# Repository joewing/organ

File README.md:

# 3D Printed Polyphonic Organ

## Features
  * Full-size 3D printed keyboard
  * 8-way polyphony
  * 9 drawbars to adjust harmonics (like a Hammond organ)
  * Sustain pedal
  * Range C0 through B7 (96 notes)

## Directories
  * src - Source code for the microcontroller (AVR ATtiny861A)
  * pcb/sensor - PCB for the key sensor board
  * pcb/controller PCB for the controller board
  * scad - OpenSCAD design

## Function Keys

Holding the "function" key on the controller PCB switches into
function mode.

### Tuning

Since we use the on-board oscillator, it is necessary to tune the
clock frequency to make the notes in tune. This tuning is stored in
EEPROM.

  * F#0 - Flatten
  * G#0 - Reset
  * A#0 - Sharpen

## 3D Printed Parts

  * Keybed
  * White keys (7)
  * Black keys (5)
  * Assembly tool (to help attach the rubber bands)
  * Control board holder

The sensor PCB is snapped into the keybed and the keys are attached,
one at a time along with the rubber band to pull the key up. Multiple
keybeds can be attached together using zipties (there are holes for
zipties in the standoff for the keys).

## BOM

  * Controller PCB
    * 1x ATtiny861A
    * 1x USB-B socket
    * 1x 2x3 IDC socket
    * 1x 3.5mm audio jack
    * 1x 3mm LED
    * 1x 6mm SPST tactile switch
    * 10x 10k linear POT
    * 2x 1k resistor
    * 12x 0.1u capacitor
    * 1x 10u capacitor
    * 1x 47u capacitor
    * 1x 6-pin right-angle socket

  * Sensor PCB (1 per octave)
    * 12x 12.6x6.5x5.7mm SPDT limit switch
    * 2x 10k resistor
    * 2x 74HC165
    * 2x 0.1uF capacitor
    * 1x 6-pin right-angle socket
    * 1x 6-pin right-angle pin header

  * Other
    * 12x small rubber bands (one set per octave)
    * USB cord and power supply

## Keys

Each note is controlled by a limit switch. The output of the limit
switches are processed serially using two 74HC165 8-bit parallel input
shift registers per octave. Since there are only 12 notes in an octave
4 bits are wasted for simplicity. Using this shift register interface,
we can read all keys using only 3 pins of the microcontroller.

In software, the state of each key is recorded in a bitmap. When a new key
press is detected, a "voice" is removed from the head of a linked list
and placed at the end of the list. The frequency increment is set
according to the index of the key that was pressed. The frequency increment
is a 16-bit value used to move through the waveform every time the
sample interrupt executes. The top 8 bits are used as an index into
the 256 entry waveform.

When a key release is detected, the "voice" is removed and placed at the
head of the list and the frequency increment is set to 0 to prevent the
sample interrupt from moving through the waveform.
The linked list is used so that the least recently pressed key is
re-used if there are too many keys pressed at the same time.

Finally, the sustain pedal simply prevents the processing of key releases.

## Drawbars

There are nine drawbars (potentiometers) that are sampled using the 
multiplexed ADC. One drawbar is sampled per iteration of the main loop.
We track the quantized value of each drawbar. When a change is
detected, its value is recorded and the waveform is recomputed.

## Waves

Waveforms are generated by sampling a 256 point sine wave.
The base waveform is at half the fundamental frequency (16')
allowing us to generate the necessary harmonics by stepping
through the sine wave at different rates:

  * 16'     - Sub-Octave (1x)
  * 5 1/3'  - Quint (3x)
  * 8'      - Principal (2x)
  * 4'      - Octave (4x)
  * 2 2/3'  - Nazard (6x)
  * 2'      - Super Octave (8x)
  * 1 3/5'  - Tierce (10x)
  * 1 1/3'  - Larigot (12x)
  * 1'      - Super-Super Octave (16x)

When a drawbar is changed, the waveform is recomputed by adding
together the scaled contributions from each drawbar. Each
contribution is determined by stepping through the sine wave at the
specified rate (2 for 8', etc), wrapping around when necessary,
and scaling the amplitude by the drawbar level. The final waveform
is scaled down by the max total contribution.
The waveform itself is stored as 256 8-bit values.

Audio is generated using 64 MHz pulse-width modulation. The duty cycle
is configured to have 256 levels, leaving an output frequency of 250 kHz,
which is well above the audio range and easy to filter. The duty cycle is
determined by adding together the waveform contributions from each voice.
Since there are 8 voices and the duty cycle is controlled by
an 8-bit value, we get 5 bits of resolution (this avoids overflow in
the case all voices are at the maximum position in the waveform at
the same time).
A 20 kHz timer interrupt causes us to move through the waveforms
for each voice and update the PWM duty cycle.

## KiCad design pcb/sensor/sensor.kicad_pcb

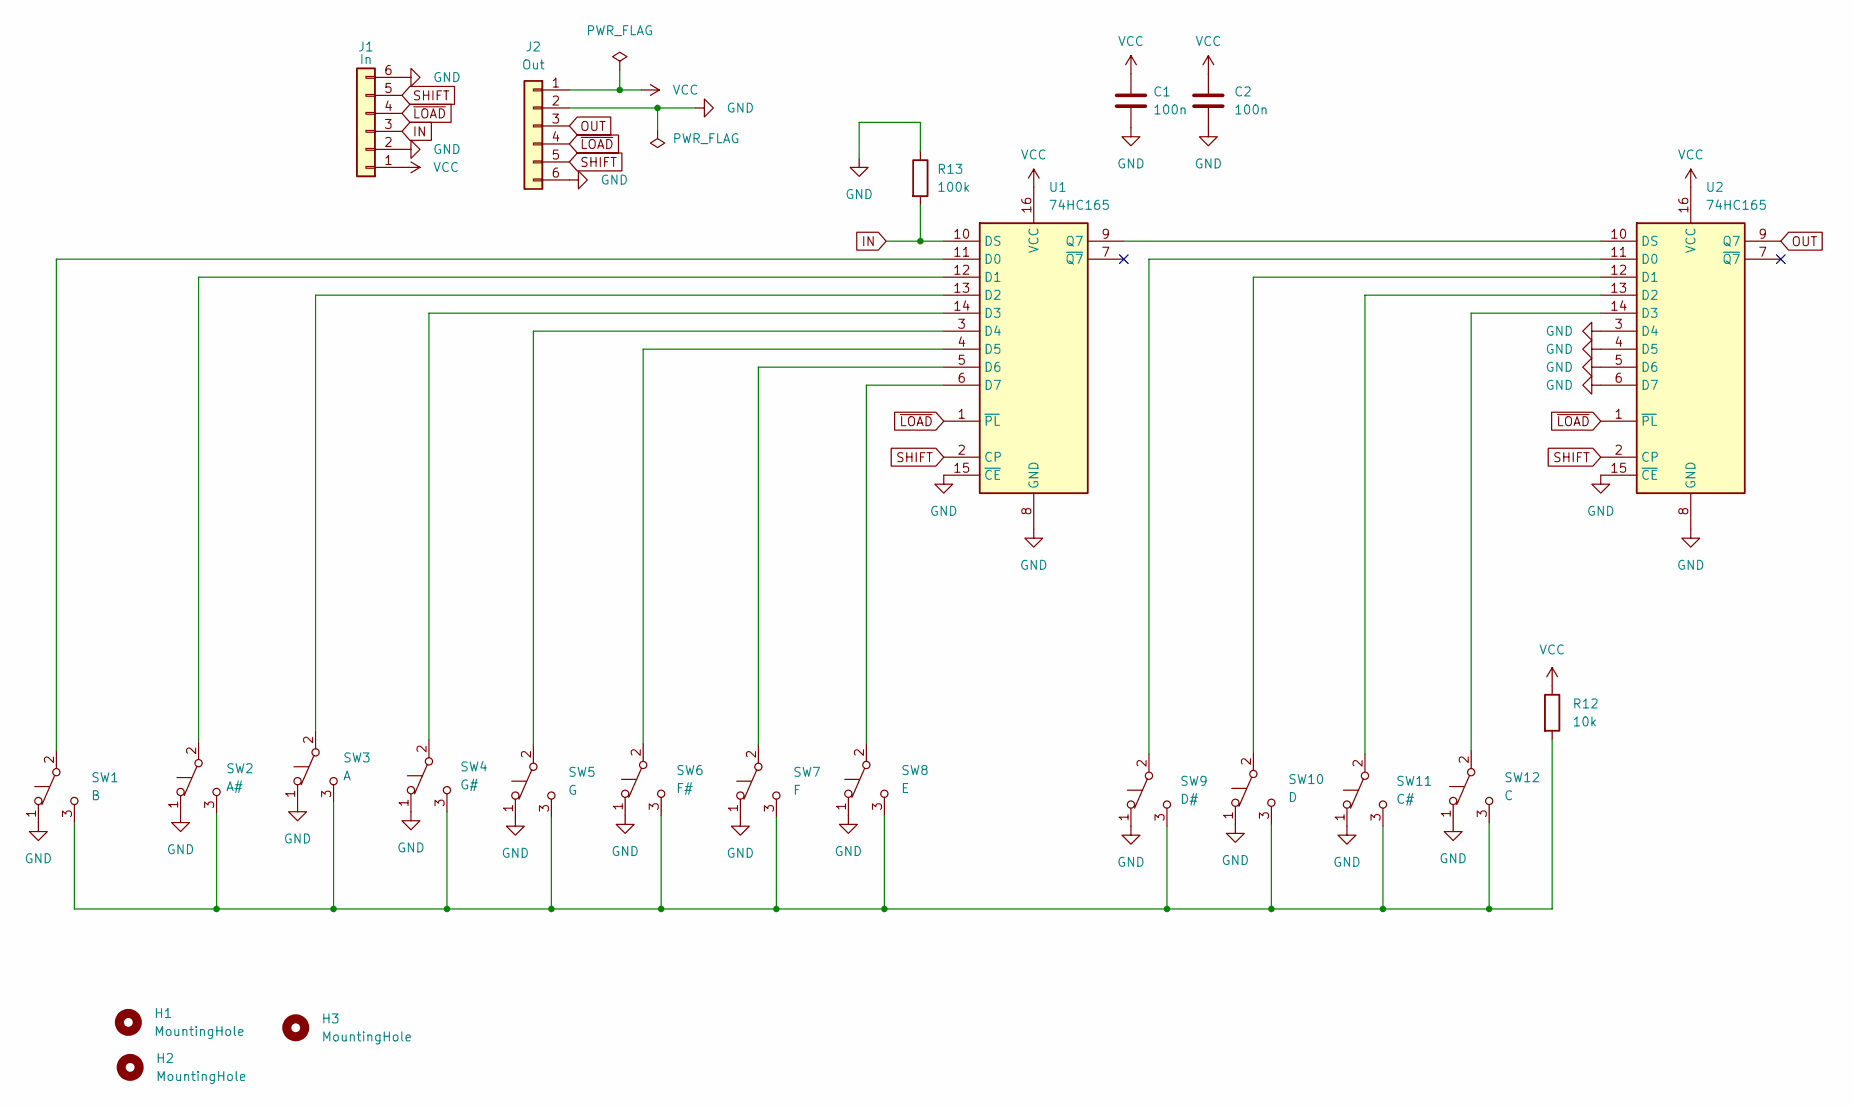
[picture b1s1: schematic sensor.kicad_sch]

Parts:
C1, C2: 100n; C_Disc_D3.0mm_W2.0mm_P2.50mm
H1, H2, H3: MountingHole; MountingHole_3.2mm_M3
J1: In; PinHeader_1x06_P2.54mm_Vertical
J2: Out; PinHeader_1x06_P2.54mm_Vertical
R12: 10k; R_Axial_DIN0207_L6.3mm_D2.5mm_P10.16mm_Horizontal
R13: 100k; R_Axial_DIN0207_L6.3mm_D2.5mm_P10.16mm_Horizontal
SW1: B; Mini Limit Switch
SW2: A#; Mini Limit Switch
SW3: A; Mini Limit Switch
SW4: G#; Mini Limit Switch
SW5: G; Mini Limit Switch
SW6: F#; Mini Limit Switch
SW7: F; Mini Limit Switch
SW8: E; Mini Limit Switch
SW9: D#; Mini Limit Switch
SW10: D; Mini Limit Switch
SW11: C#; Mini Limit Switch
SW12: C; Mini Limit Switch
U1, U2: 74HC165; DIP-16_W7.62mm_Socket

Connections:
GND: C1.2, C2.2, J1.2, J1.6, J2.2, J2.6, R13.1, SW1.1 (A), SW2.1 (A), SW3.1 (A), SW4.1 (A), SW5.1 (A), SW6.1 (A), SW7.1 (A), SW8.1 (A), SW9.1 (A), SW10.1 (A), SW11.1 (A), SW12.1 (A), U1.8 (GND), U1.15 (~CE), U2.3 (D4), U2.4 (D5), U2.5 (D6), U2.6 (D7), U2.8 (GND), U2.15 (~CE)
IN: J1.3, R13.2, U1.10 (DS)
unnamed: R12.2, SW1.3 (C), SW2.3 (C), SW3.3 (C), SW4.3 (C), SW5.3 (C), SW6.3 (C), SW7.3 (C), SW8.3 (C), SW9.3 (C), SW10.3 (C), SW11.3 (C), SW12.3 (C)
unnamed: SW1.2 (B), U1.11 (D0)
unnamed: SW2.2 (B), U1.12 (D1)
unnamed: SW3.2 (B), U1.13 (D2)
unnamed: SW4.2 (B), U1.14 (D3)
unnamed: SW5.2 (B), U1.3 (D4)
unnamed: SW6.2 (B), U1.4 (D5)
unnamed: SW7.2 (B), U1.5 (D6)
unnamed: SW8.2 (B), U1.6 (D7)
unnamed: SW9.2 (B), U2.11 (D0)
unnamed: SW10.2 (B), U2.12 (D1)
unnamed: SW11.2 (B), U2.13 (D2)
unnamed: SW12.2 (B), U2.14 (D3)
unnamed: U1.9 (Q7), U2.10 (DS)
OUT: J2.3, U2.9 (Q7)
SHIFT: J1.5, J2.5, U1.2 (CP), U2.2 (CP)
VCC: C1.1, C2.1, J1.1, J2.1, R12.1, U1.16 (VCC), U2.16 (VCC)
~LOAD: J1.4, J2.4, U1.1 (~PL), U2.1 (~PL)

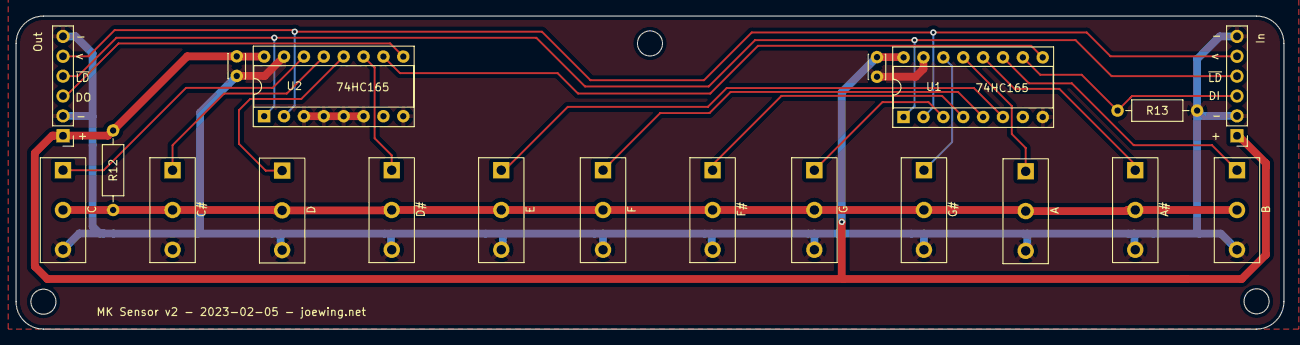
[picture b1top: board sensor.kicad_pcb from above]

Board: 2 copper layers, 162.0 x 40.0 mm, 23 parts (0 on the bottom side), 20 nets.

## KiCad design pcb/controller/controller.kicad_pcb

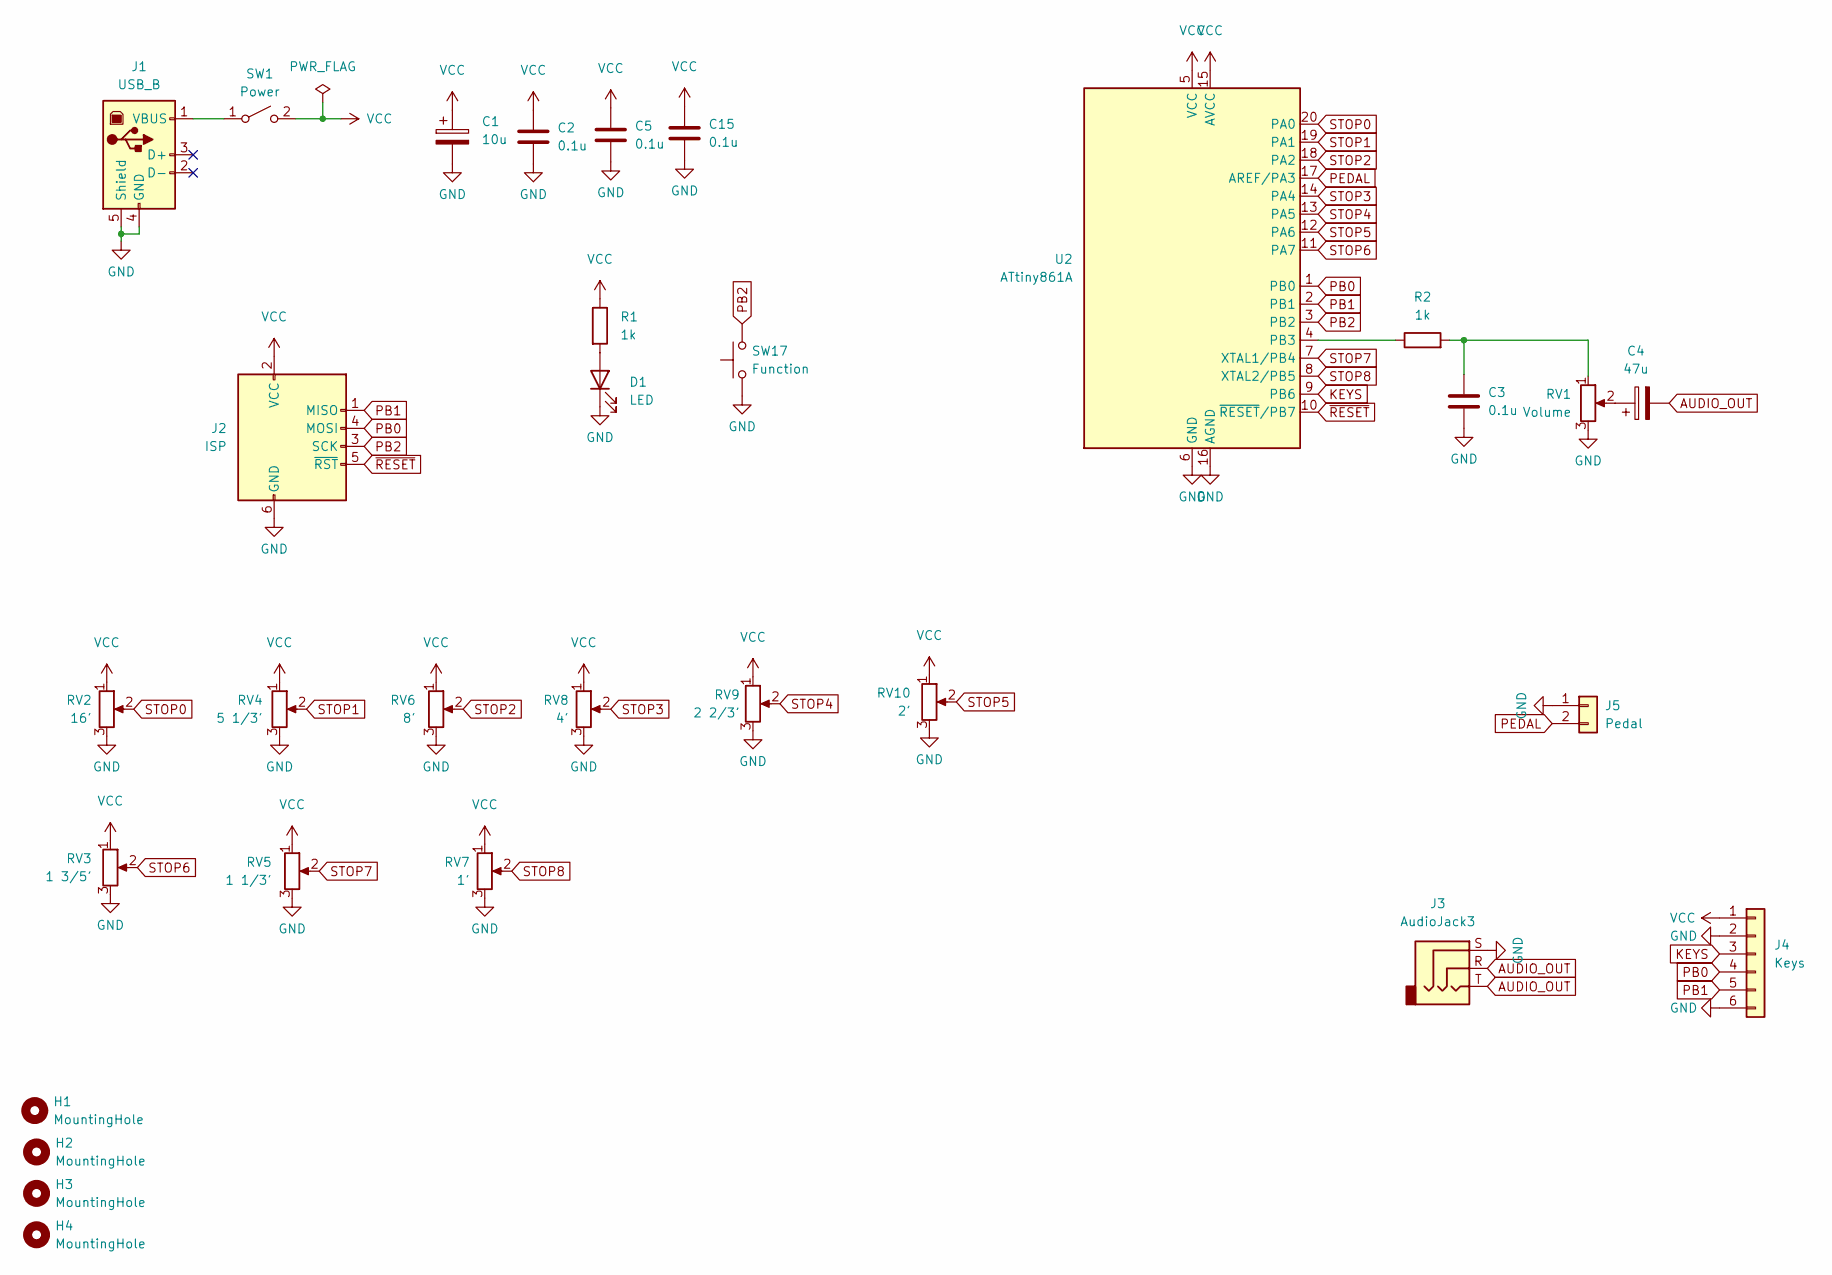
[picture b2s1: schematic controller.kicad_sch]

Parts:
C1: 10u; CP_Radial_D5.0mm_P2.00mm; LCSC C15850
C2, C3, C5, C15: 0.1u; C_Disc_D3.0mm_W2.0mm_P2.50mm; LCSC C49678
C4: 47u; CP_Radial_D5.0mm_P2.00mm; LCSC C15850
D1: LED; LED_D3.0mm; LCSC C2297
H1, H2, H3, H4: MountingHole; MountingHole_3.2mm_M3
J1: USB_B; USB_B_OST_USB-B1HSxx_Horizontal
J2: ISP; IDC-Header_2x03_P2.54mm_Vertical
J3: AudioJack3; Jack_3.5mm_CUI_SJ1-3523N_Horizontal
J4: Keys; PinHeader_1x06_P2.54mm_Vertical
J5: Pedal; PinHeader_1x02_P2.54mm_Vertical
R1, R2: 1k; R_Axial_DIN0309_L9.0mm_D3.2mm_P15.24mm_Horizontal; LCSC C17513
RV1: Volume; Potentiometer_Bourns_PTA3043_Single_Slide
RV2: 16'; Potentiometer_Bourns_PTA3043_Single_Slide
RV3: 1 3/5'; Potentiometer_Bourns_PTA3043_Single_Slide
RV4: 5 1/3'; Potentiometer_Bourns_PTA3043_Single_Slide
RV5: 1 1/3'; Potentiometer_Bourns_PTA3043_Single_Slide
RV6: 8'; Potentiometer_Bourns_PTA3043_Single_Slide
RV7: 1'; Potentiometer_Bourns_PTA3043_Single_Slide
RV8: 4'; Potentiometer_Bourns_PTA3043_Single_Slide
RV9: 2 2/3'; Potentiometer_Bourns_PTA3043_Single_Slide
RV10: 2'; Potentiometer_Bourns_PTA3043_Single_Slide
SW1: Power; PinHeader_1x03_P2.54mm_Vertical
SW17: Function; SW_PUSH_6mm
U2: ATtiny861A; DIP-20_W7.62mm

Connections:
AUDIO_OUT: C4.2, J3.R, J3.T
GND: C1.2, C2.2, C3.2, C5.2, C15.2, D1.1 (K), J1.4 (GND), J1.5 (Shield), J2.6 (GND), J3.S, J4.2, J4.6, J5.1, RV1.3, RV2.3, RV3.3, RV4.3, RV5.3, RV6.3, RV7.3, RV8.3, RV9.3, RV10.3, SW17.1, U2.6 (GND), U2.16 (AGND)
KEYS: J4.3, U2.9 (PB6)
unnamed: C3.1, R2.2, RV1.1
unnamed: C4.1, RV1.2
unnamed: D1.2 (A), R1.2
unnamed: J1.1 (VBUS), SW1.1 (A)
unnamed: R2.1, U2.4 (PB3)
PB0: J2.4 (MOSI), J4.4, U2.1 (PB0)
PB1: J2.1 (MISO), J4.5, U2.2 (PB1)
PB2: J2.3 (SCK), SW17.2, U2.3 (PB2)
PEDAL: J5.2, U2.17 (AREF/PA3)
STOP0: RV2.2, U2.20 (PA0)
STOP1: RV4.2, U2.19 (PA1)
STOP2: RV6.2, U2.18 (PA2)
STOP3: RV8.2, U2.14 (PA4)
STOP4: RV9.2, U2.13 (PA5)
STOP5: RV10.2, U2.12 (PA6)
STOP6: RV3.2, U2.11 (PA7)
STOP7: RV5.2, U2.7 (XTAL1/PB4)
STOP8: RV7.2, U2.8 (XTAL2/PB5)
VCC: C1.1, C2.1, C5.1, C15.1, J2.2 (VCC), J4.1, R1.1, RV2.1, RV3.1, RV4.1, RV5.1, RV6.1, RV7.1, RV8.1, RV9.1, RV10.1, SW1.2 (B), U2.5 (VCC), U2.15 (AVCC)
~RESET: J2.5 (~RST), U2.10 (~RESET/PB7)

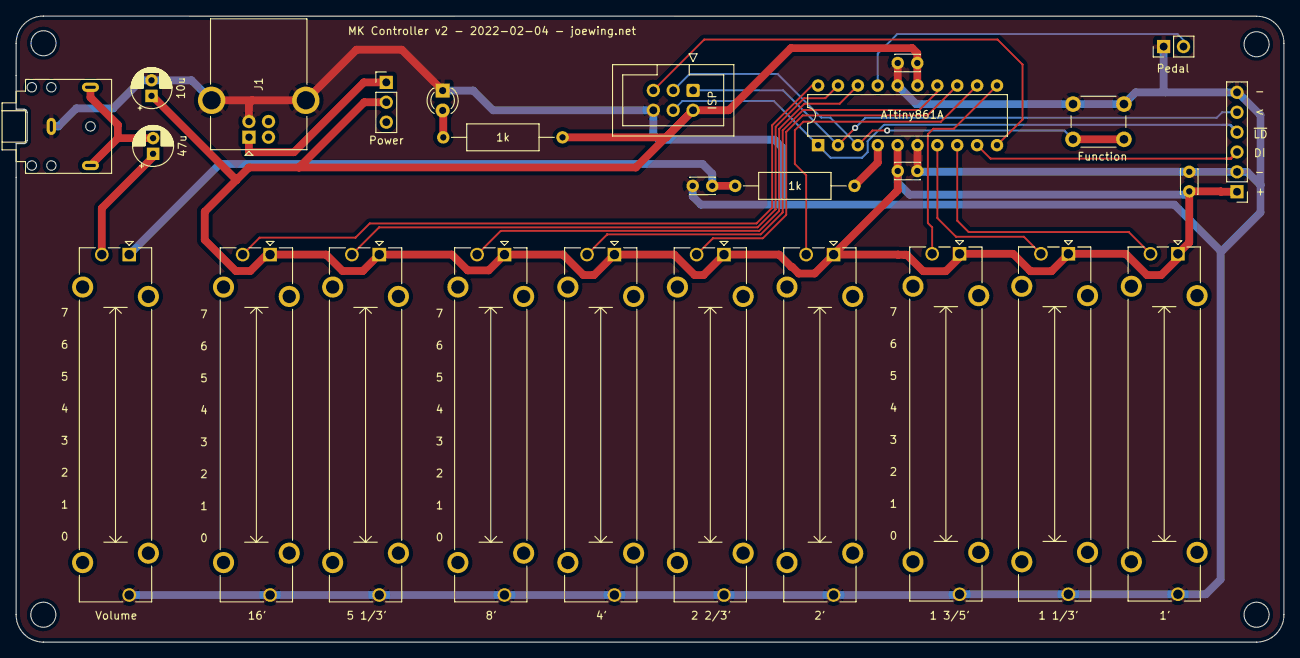
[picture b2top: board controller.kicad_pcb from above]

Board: 2 copper layers, 162.0 x 80.0 mm, 31 parts (0 on the bottom side), 23 nets.

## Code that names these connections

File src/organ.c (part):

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#define INITIAL_OCTAVE    1       // Initial lowest physical octave

#ifdef ATTINY861A
#define KEY_LATCH_PIN PB0
#define KEY_CLOCK_PIN PB1
#define FUN_INPUT_PIN PB2
#define AUDIO_OUT_PIN PB3
#define KEY_INPUT_PIN PB6
#else
#define KEY_LATCH_PIN PB0
#define KEY_CLOCK_PIN PB1
#define FUN_INPUT_PIN PB2
#define KEY_INPUT_PIN PB3
#define AUDIO_OUT_PIN PB4
#endif

#define VOICE_COUNT         (1 << VOICE_BITS)
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
  const uint8_t control = (~PINB) & (1 << FUN_INPUT_PIN);
#ifdef ATTINY861A
  const uint8_t sustain = (~PINA) & (1 << PA3);
#else
  const uint8_t sustain = 0;
#endif
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  PLLCSR |= (1 << PLLE);

  // Set input pullups and output state.
  PORTA = (1 << PA3);
  PORTB = (1 << KEY_INPUT_PIN)
        | (1 << FUN_INPUT_PIN);

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  DDRA = 0;
  DDRB = (1 << KEY_LATCH_PIN)
       | (1 << KEY_CLOCK_PIN)
       | (1 << AUDIO_OUT_PIN);

  // PWM timer setup (timer1)
  // This timer uses high-frequency PWM to generate the amplitude of
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  // Set up ADC for drawbars.
  ADMUX   = (0 << REFS0)  // Vcc reference
          | (1 << ADLAR)  // Left adjust (we only need 8 bits of resolution)
          | (0 << MUX0);  // ADC0 - PA0
  ADCSRA  = (1 << ADEN)   // Enable ADC
          | (0 << ADSC)   // Don't start yet.
          | (0 << ADATE)  // Disable auto-trigger
          | (0 << ADIE)   // Disable interupt
          | (7 << ADPS0); // Divide by 128
  DIDR0   = (1 << ADC0D)  // Disable digital input for ADC0 - PA0
          | (1 << ADC1D)  // Disable digital input for ADC1 - PA1
          | (1 << ADC2D)  // Disable digital input for ADC2 - PA2
          | (0 << AREFD)  // Enable digital input for  AREF - PA3
          | (1 << ADC3D)  // Disable digital input for ADC3 - PA4
          | (1 << ADC4D)  // Disable digital input for ADC4 - PA5
          | (1 << ADC5D)  // Disable digital input for ADC5 - PA6
          | (1 << ADC6D); // Disable digital input for ADC6 - PA7
  DIDR1   = (1 << ADC7D)  // Disable digital input for ADC7 - PB4
          | (1 << ADC8D); // Disable digital input for ADC8 - PB5
  ADCSRA |= (1 << ADSC);  // Start

#else
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  // Set outputs.
  DDRB = (1 << KEY_LATCH_PIN)
       | (1 << KEY_CLOCK_PIN)
       | (1 << AUDIO_OUT_PIN);

  // PWM timer setup (timer1)
  PLLCSR = (1 << PCKE) | (1 << PLLE);   // 64MHz PLL source for timer1
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
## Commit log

2023-01-09 Update key sizes.
2023-01-11 Sensor v0
2023-01-12 Update keybed.
2023-01-21 Checkpoint
2023-01-21 Clips
2023-01-21 Move hole
2023-01-22 Boards ordered.
2023-01-22 Move stuff around.
2023-02-05 Save
2023-02-27 Better tolerances.
2023-03-19 Add STLs.
